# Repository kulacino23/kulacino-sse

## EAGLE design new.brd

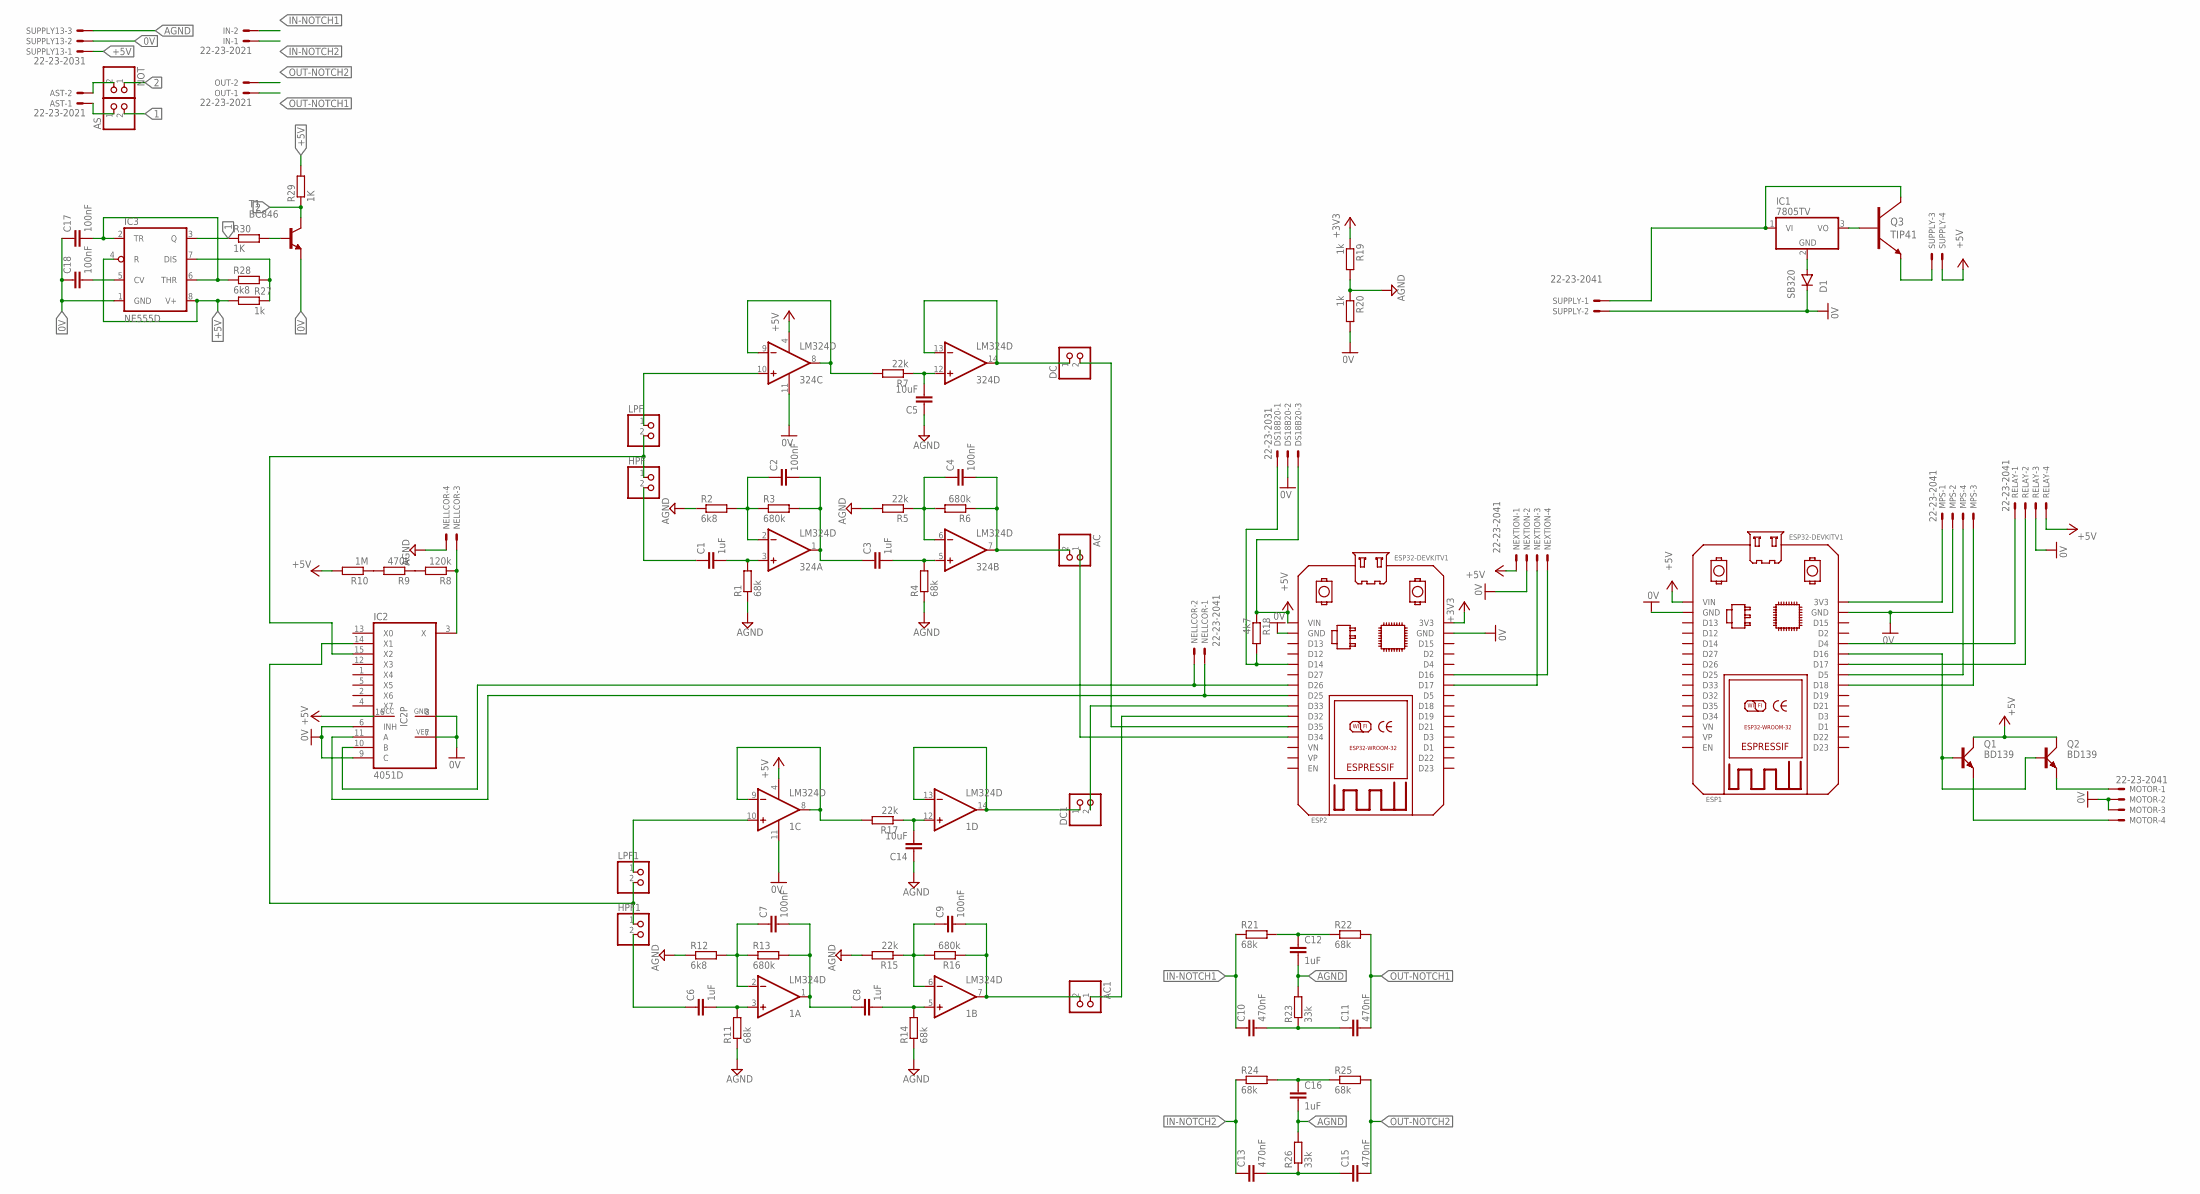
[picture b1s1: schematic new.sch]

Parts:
1, 324: LM324D; SO14
AC, AC1: PINHD-1X2; 1X02
AS: PINHD-1X2; 1X02
AST: 22-23-2021
C1, C3, C6, C8, C12, C16: 1uF; C0603
C2, C4, C7, C9, C17, C18: 100nF; C0603
C5, C14: 10uF; C0603
C10, C11, C13, C15: 470nF; C0603
D1: SB320; DO201-15
DC, DC1: PINHD-1X2; 1X02
DS18B20: 22-23-2031
ESP1, ESP2: ESP32DEVKITV1; ESP32-DEVKITV1
HPF, HPF1: PINHD-1X2; 1X02
IC1: 7805TV; TO220V
IC2: 4051D; SO16
IC3: NE555D; SO08
IN: 22-23-2021
LPF, LPF1: PINHD-1X2; 1X02
MOTOR: 22-23-2041
MPS: 22-23-2041
NELLCOR: 22-23-2041
NEXTION: 22-23-2041
NOT: PINHD-1X2; 1X02
OUT: 22-23-2021
Q1, Q2: BD139; TO126AV
Q3: TIP41; TO-220AB
R1, R4, R11, R14, R21, R22, R24, R25: 68k; R0603
R2, R12, R28: 6k8; R0603
R3, R6, R13, R16: 680k; R0603
R5, R7, R15, R17: 22k; R0603
R8: 120k; R0603
R9: 470k; R0603
R10: 1M; R0603
R18: 4k7; R0603
R19, R20, R27: 1k; R0603
R23, R26: 33k; R0603
R29, R30: 1K; R0603
RELAY: 22-23-2041
SUPPLY: 22-23-2041
SUPPLY13: 22-23-2031
T1: BC846; SOT23

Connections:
0V: 1.11 (V-), 324.11 (V-), C17.1, C18.1, D1.C, DS18B20.2, ESP1.GND, ESP1.GND@1 (GND), ESP2.GND, ESP2.GND@1 (GND), IC2.6 (INH), IC2.7 (VEE), IC2.8 (GND), IC2.9 (C), IC3.1 (GND), MOTOR.2, MOTOR.3, MPS.2, NEXTION.2, R20.2, RELAY.3, SUPPLY.2, SUPPLY13.2, T1.2 (E)
1: AS.2, IC3.3 (Q), R30.1
2: NOT.1, R29.1, T1.3 (C)
+3V3: ESP2.3V3, R19.1
+5V: 1.4 (V+), 324.4 (V+), DS18B20.3, ESP1.VIN, ESP2.VIN, IC2.16 (VCC), IC3.4 (R), IC3.8 (V+), NEXTION.1, Q1.C, Q2.C, R10.2, R18.1, R27.1, R29.2, RELAY.4, SUPPLY.4, SUPPLY13.1
AGND: C5.1, C12.2, C14.1, C16.2, NELLCOR.4, R1.1, R2.1, R4.1, R5.2, R11.1, R12.1, R14.1, R15.2, R19.2, R20.1, R23.2, R26.2, SUPPLY13.3
IN-NOTCH1: C10.1, IN.2, R21.1
IN-NOTCH2: C13.1, IN.1, R24.1
unnamed: 324.3 (+IN), C1.2, R1.2
unnamed: 324.5 (+IN), C3.2, R4.2
unnamed: 324.6 (-IN), C4.1, R5.1, R6.2
unnamed: 324.7 (OUT), AC.2, C4.2, R6.1
unnamed: 324.1 (OUT), C2.2, C3.1, R3.2
unnamed: 324.2 (-IN), C2.1, R2.2, R3.1
unnamed: 324.8 (OUT), 324.9 (-IN), R7.2
unnamed: 324.12 (+IN), C5.2, R7.1
unnamed: 324.13 (-IN), 324.14 (OUT), DC.1
unnamed: 324.10 (+IN), LPF.1
unnamed: ESP2.D26, IC2.10 (B), NELLCOR.2
unnamed: IC2.3 (X), NELLCOR.3, R8.1
unnamed: R8.2, R9.1
unnamed: C1.1, HPF.2
unnamed: 1.3 (+IN), C6.2, R11.2
unnamed: 1.6 (-IN), C9.1, R15.1, R16.2
unnamed: DC1.2, ESP2.D33
unnamed: R9.2, R10.1
unnamed: ESP1.3V3, MPS.1
unnamed: 1.7 (OUT), AC1.2, C9.2, R16.1
unnamed: 1.1 (OUT), C7.2, C8.1, R13.2
unnamed: ESP2.D16, NEXTION.4
unnamed: 1.2 (-IN), C7.1, R12.2, R13.1
unnamed: HPF.1, IC2.15 (X2), LPF.2
unnamed: 1.8 (OUT), 1.9 (-IN), R17.2
unnamed: 1.5 (+IN), C8.2, R14.2
unnamed: HPF1.1, IC2.14 (X1), LPF1.2
unnamed: ESP1.D17, RELAY.2
unnamed: ESP1.D5, MPS.4
unnamed: ESP1.D18, MPS.3
unnamed: ESP1.D4, RELAY.1
unnamed: ESP2.D25, IC2.11 (A), NELLCOR.1
unnamed: 1.12 (+IN), C14.2, R17.1
unnamed: 1.13 (-IN), 1.14 (OUT), DC1.1
unnamed: ESP1.D16, Q1.B, Q2.B
unnamed: DC.2, ESP2.D35
unnamed: AC1.1, ESP2.D32
unnamed: 1.10 (+IN), LPF1.1
unnamed: C6.1, HPF1.2
unnamed: AC.1, ESP2.D34
unnamed: DS18B20.1, ESP2.D14, R18.2
unnamed: ESP2.D17, NEXTION.3
unnamed: MOTOR.1, Q2.E
unnamed: MOTOR.4, Q1.E
unnamed: IC1.1 (VI), Q3.2 (C), SUPPLY.1
unnamed: IC1.3 (VO), Q3.1 (B)
unnamed: Q3.3 (E), SUPPLY.3
unnamed: D1.A, IC1.2 (GND)
unnamed: C12.1, R21.2, R22.1
unnamed: C10.2, C11.1, R23.1
unnamed: C16.1, R24.2, R25.1
unnamed: C13.2, C15.1, R26.1
unnamed: C17.2, IC3.2 (TR), IC3.6 (THR), R28.1
unnamed: IC3.7 (DIS), R27.2, R28.2
unnamed: C18.2, IC3.5 (CV)
unnamed: R30.2, T1.1 (B)
unnamed: AST.2, NOT.2
unnamed: AS.1, AST.1
OUT-NOTCH1: C11.2, OUT.1, R22.2
OUT-NOTCH2: C15.2, OUT.2, R25.2

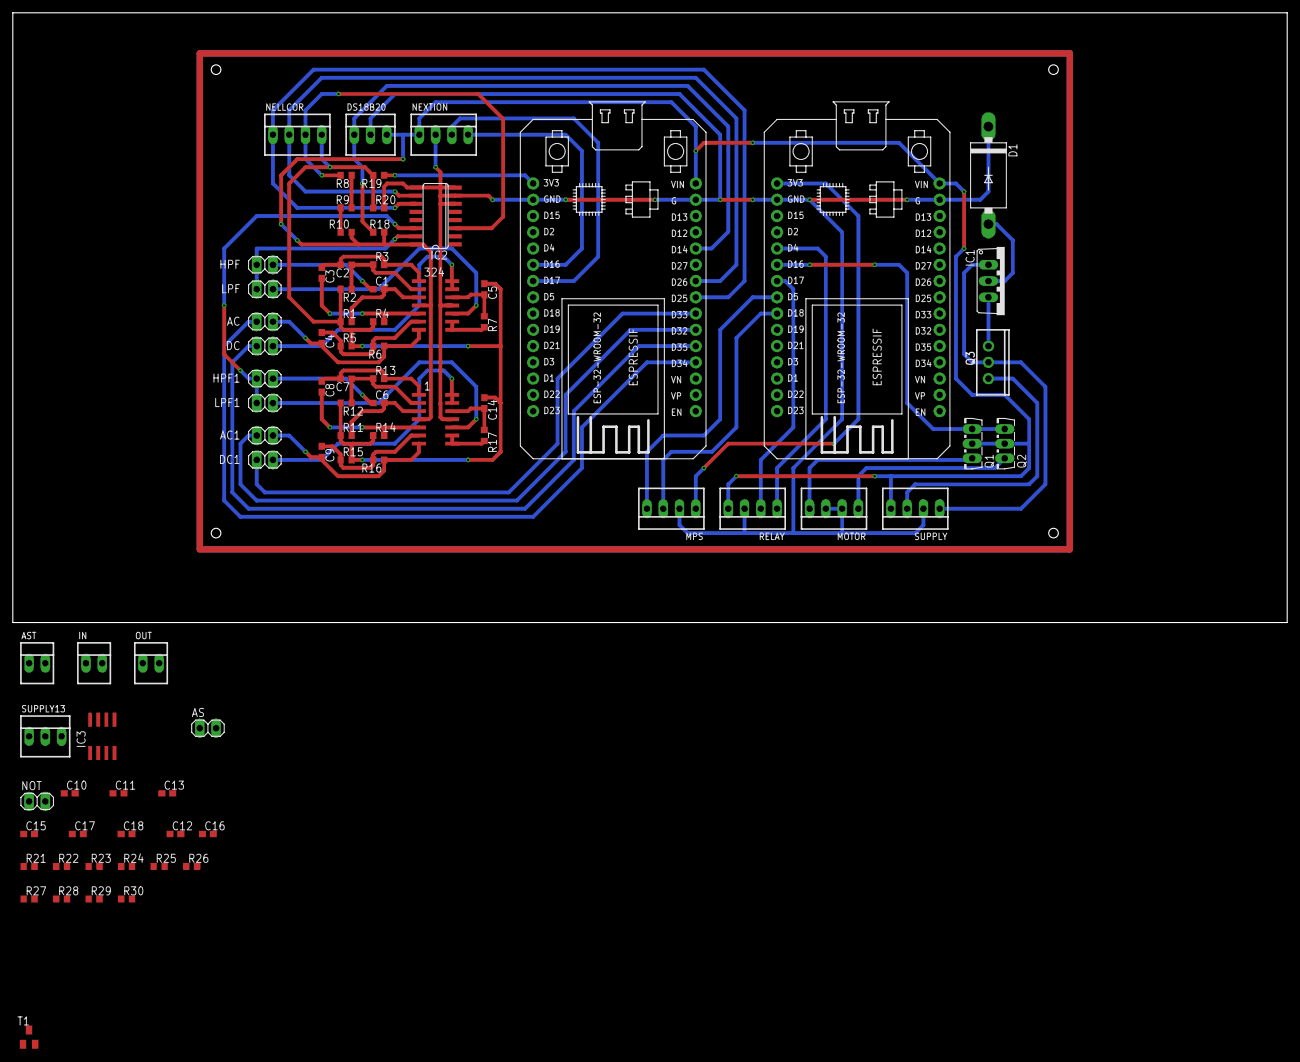
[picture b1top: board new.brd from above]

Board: 2 copper layers, 199.1 x 95.2 mm, 81 parts (0 on the bottom side), 68 nets.
